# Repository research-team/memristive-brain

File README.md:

# Robot Dream: Memristive brain project ENDSTOP!!!!!

## Problem

The memristive brain project is dedicated to the reimplementation of bio-plausible emotional drives based behavioral strategies in a robotic system, in the other words to solve the embodiment problem for the simulated brain in HPC system. 

During the [NeuCogAr](https://github.com/research-team/NEUCOGAR) project we have managed to develop mammalian emotional drives potential basement for decision making over behavioral strategies. We are doing the validation of overall model of 8 basic emotional states: fear, joy, disgust, humiliation, anger, interest, surprise, distress based on three neuromodulators: noradrenaline, dopamine and serotonin and currently we have managed to validate two states: fear-like and disgust-like. 

The problem is that the bio-plausible simulation of a mammalian brain is really slow and can not be used for real-time processing, but robotic embodiment should be operating real-time. We have started the [Robot Dream](https://github.com/research-team/robot-dream) project to solve this problem still keeping bio-plausibility in integration with real-time robotic system.

A robotic system management system could be implemented using several approaches including reimplementation of mammalian brain structures in electronic schematic. To implement this we have started from the memristive solution of a neuron. Starting from the beginning of 2017 we are developing a memristive implementation of bio-plausible neuronal inhibition and neuromodulation.

The complete documentation on memristive approach could be found [here](https://github.com/research-team/memristive-brain/blob/master/doc/memristive_approach.md).

# Breakthrough 

**AI and robotics**: New architectures of robotic systems, based on the integration of memory and processor in a single chip, capable of memorizing the information and changing accordingly connections between elements within processor will be implemented. This system will be significantly different from the existing computers/robots. The proposed architecture of new generation of robots will be capable of self learning and will not be using traditional software approaches making software development obsolete.

**Brain science/neurophysiology**: In the case of success, neurophysiology will acquire a new tool for modeling of processes in nervous system and brain. An integration of living (neurons) and not living memristive elements will be combined in a hybrid system.This tool will provide an option to better understand processes of the reinforcement and inhibition of signal pathways during supervised and unsupervised learning. Memristors eliminate all physical restrictions of learning algorithms; they allow to “switch off” learning of selected elements, allowing the creation of new neuromorphic machine learning algorithms. 

From the **bionics** perspective, memristor-based artificial synapses could be a part of implantable controllers for artificial organs and prosthesis.
Apart from the breakthrough in the main direction of the research, mentioned above, we expect also to have fundamental results in the following branches:

**Physics/electronics**: The project results will allow to better understand processes, occurring in different memristive devices – new perspective electronic elements. Technological processes of the production of such elements and circuits, as well as processors – memory elements based on them will be developed.  We suppose that the investigation and development of memristive devices could result to the revolution in electronic and computer industries. “Being combined with transistors into hybrid chips, memristors could improve radically properties of digital circuits, without the removal of transistors.
 More effective utilization of transistors could allow to improve properties according to the Moor low, at least during next 10 years, without expensive and becoming continuously more complicated increasing of the integration level in the chip. Finally, memristors could be even a basic stone of new analog circuits, making calculations using the architecture, similar to that of the brain”. [William R.S., How We Found the Missing Memristor. IEEE Spectrum 2008-12-18]. Taking into consideration a grate and continuously increasing interest of scientific centers and commercial laboratories to the implementation of memristors, it is possible to predict that in 5-10 years memristors will be one of the most common elements of electronic circuits.

**Material science/self organization**: it will be investigated new polymer-based materials, allowing to organize structures with distributed electrical properties for the utilization as matrices with adaptive properties.

# Folder structure

+ **demo-stand** - contains info about current measuremet schematic. Now not used.
+ **doc** - contains all required documentation
+ **ltspice_libs** - contains all additional components, used in LTSPICE schematics
+ **memristors** - contains information about memristors, used in project
+ **test-circuits** - contains all electrical schematics, connected with this project

[This video](https://youtu.be/JvsyhsOdTj8) contains all info, related to current circuits.

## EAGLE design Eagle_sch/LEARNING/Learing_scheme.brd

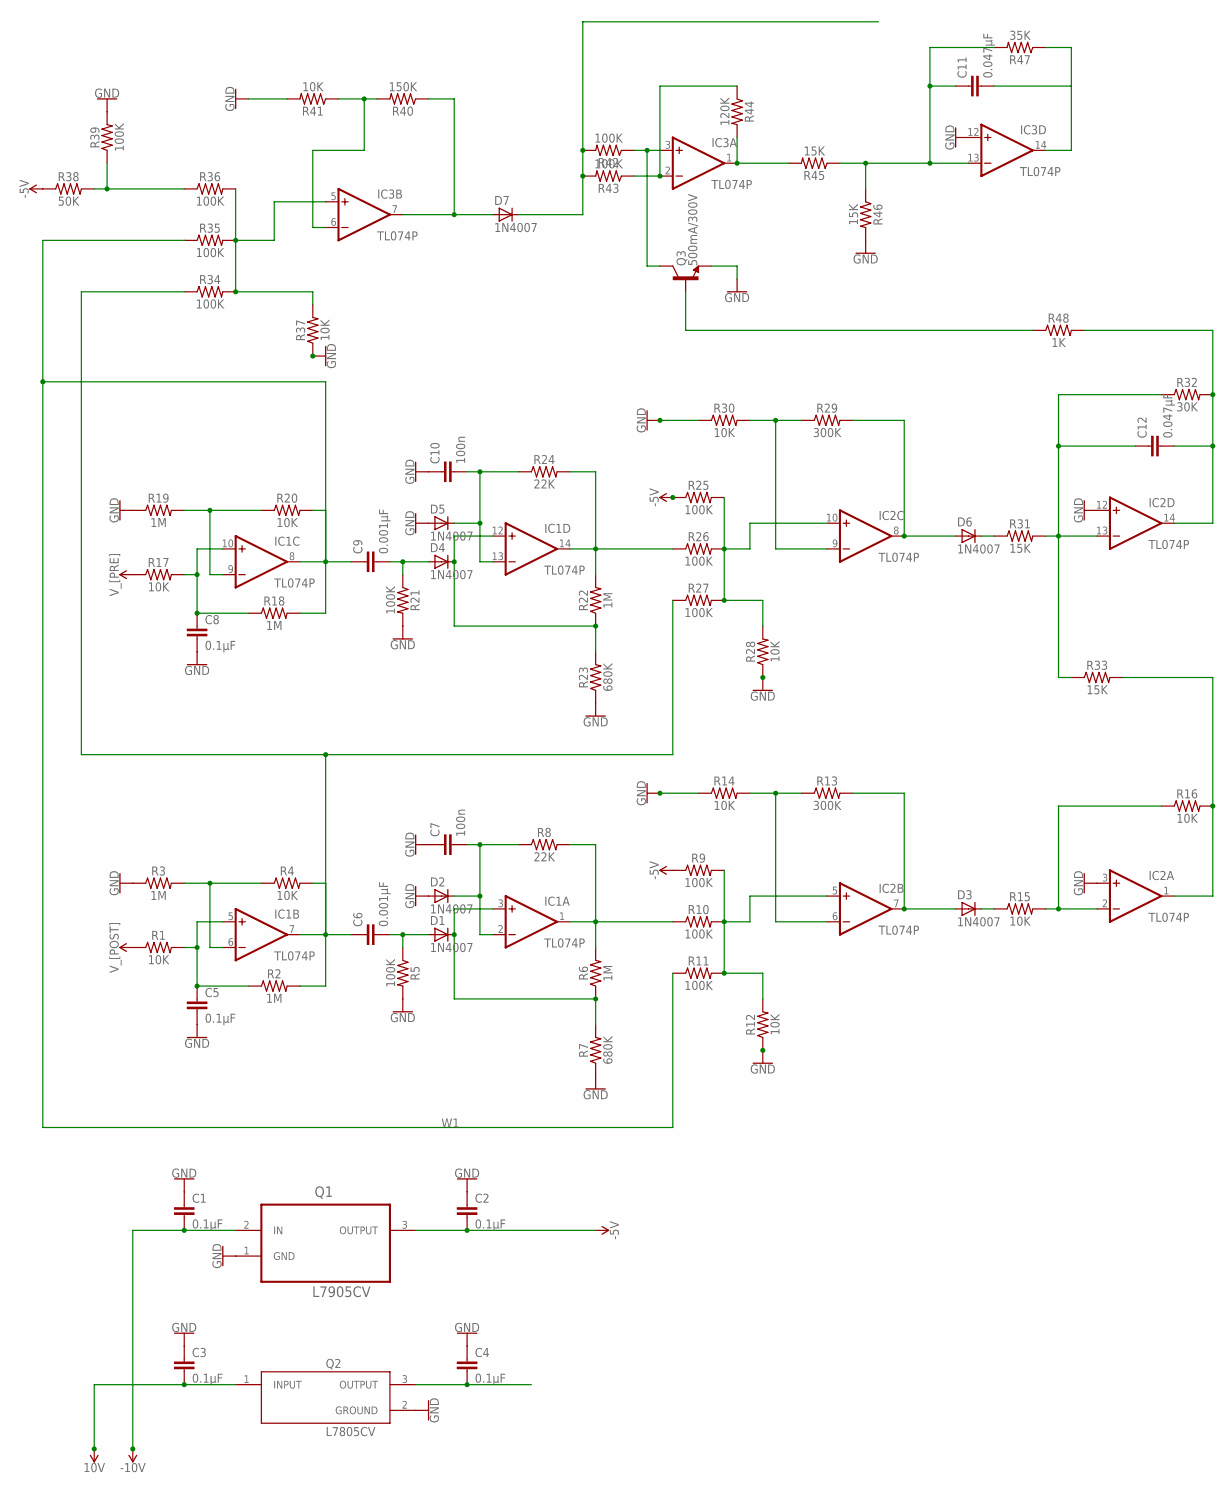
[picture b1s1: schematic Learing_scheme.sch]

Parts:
C1, C2, C3, C4, C5, C8: 0.1µF; 0805
C6, C9: 0.001µF; 0805
C7, C10: 100n; 0805
C11, C12: 0.047µF; 0805
D1, D2, D3, D4, D5, D6, D7: 1N4007; SMA
IC1, IC2, IC3: TL074P; DIL14
Q1: L7905CV; TO254P450X1020X1935-3P
Q2: L7805CV; TO255P1040X460X1968-3
Q3: 500mA/300V; SOT23-3
R1, R4, R12, R14, R15, R16, R17, R20, R28, R30, R37, R41: 10K; 0805
R2, R3, R6, R18, R19, R22: 1M; 0805
R5, R9, R10, R11, R21, R25, R26, R27, R34, R35, R36, R39, R42, R43: 100K; 0805
R7, R23: 680K; 0805
R8, R24: 22K; 0805
R13, R29: 300K; 0805
R31, R33, R45, R46: 15K; 0805
R32: 30K; 0805
R38: 50K; 0805
R40: 150K; 0805
R44: 120K; 0805
R47: 35K; 0805
R48: 1K; 0805

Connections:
12V: C1.2, C2.2, C3.2, Q1.2 (IN), Q1.3 (OUTPUT), Q2.1 (INPUT), R1.1, R9.1, R17.1, R25.1, R38.1
GND: C1.1, C2.1, C3.1, C4.1, C5.2, C7.1, C8.2, C10.1, D2.A, D5.A, IC2.3 (+IN), IC2.12 (+IN), IC3.12 (+IN), Q1.1 (GND), Q2.2 (GROUND), Q3.2 (E), R3.1, R5.2, R7.1, R12.1, R19.1, R21.2, R23.1, R28.1, R37.1, R39.2, R41.2, R46.2
unnamed: C5.1, IC1.5 (+IN), R1.2, R2.1
unnamed: C6.1, IC1.7 (OUT), R2.2, R4.2, R27.1, R34.1
unnamed: IC1.6 (-IN), R3.2, R4.1
unnamed: C4.2, Q2.3 (OUTPUT)
unnamed: D7.A, IC3.7 (OUT), R40.1
unnamed: C6.2, D1.A, R5.1
unnamed: C7.2, D2.K (C), IC1.2 (-IN), R8.1
unnamed: IC1.1 (OUT), R6.2, R8.2, R10.1
unnamed: D1.K (C), IC1.3 (+IN), R6.1, R7.2
unnamed: IC2.5 (+IN), R9.2, R10.2, R11.2, R12.2
unnamed: D3.A, IC2.7 (OUT), R13.2
unnamed: IC2.6 (-IN), R13.1, R14.2
unnamed: D3.K (C), R15.1
unnamed: IC2.2 (-IN), R15.2, R16.1
unnamed: IC2.1 (OUT), R16.2, R33.2
unnamed: C8.1, IC1.10 (+IN), R17.2, R18.1
unnamed: IC3.5 (+IN), R34.2, R35.2, R36.2, R37.2
unnamed: IC1.9 (-IN), R19.2, R20.1
unnamed: C9.2, D4.A, R21.1
unnamed: IC1.14 (OUT), R22.2, R24.2, R26.1
unnamed: D4.K (C), IC1.12 (+IN), R22.1, R23.2
unnamed: C10.2, D5.K (C), IC1.13 (-IN), R24.1
unnamed: IC2.10 (+IN), R25.2, R26.2, R27.2, R28.2
unnamed: D6.A, IC2.8 (OUT), R29.2
unnamed: IC2.9 (-IN), R29.1, R30.2
unnamed: D6.K (C), R31.1
unnamed: C12.1, IC2.13 (-IN), R31.2, R32.1, R33.1
unnamed: C12.2, IC2.14 (OUT), R32.2, R48.2
unnamed: R36.1, R38.2, R39.1
unnamed: IC3.6 (-IN), R40.2, R41.1
unnamed: IC3.3 (+IN), Q3.3 (C), R42.1
unnamed: D7.K (C), R42.2, R43.2
unnamed: IC3.2 (-IN), R43.1, R44.1
unnamed: IC3.1 (OUT), R44.2, R45.2
unnamed: C11.2, IC3.14 (OUT), R47.1
unnamed: C11.1, IC3.13 (-IN), R45.1, R46.1, R47.2
unnamed: Q3.1 (B), R48.1
V+: IC1.4 (V+), IC2.4 (V+), IC3.4 (V+)
V-: IC1.11 (V-), IC2.11 (V-), IC3.11 (V-)
W1: C9.1, IC1.8 (OUT), R11.1, R18.2, R20.2, R35.1

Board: 2 copper layers, 73 parts (0 on the bottom side), 42 nets, no tracks yet.

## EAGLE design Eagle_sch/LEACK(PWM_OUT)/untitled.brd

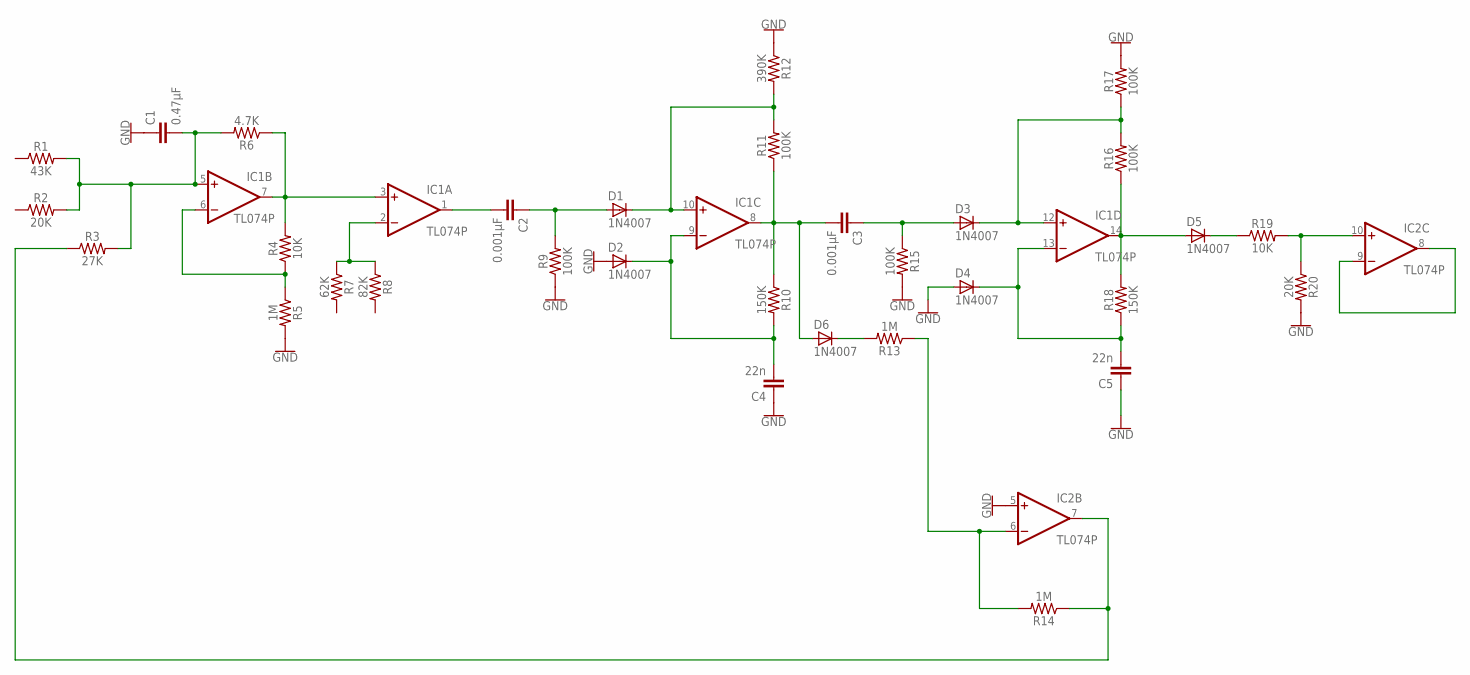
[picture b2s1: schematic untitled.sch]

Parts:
C1: 0.47µF; 0805
C2, C3: 0.001µF; 0805
C4, C5: 22n; 0805
D1, D2, D3, D4, D5, D6: 1N4007; SMA
IC1, IC2: TL074P; DIL14
R1: 43K; 0805
R2, R20: 20K; 0805
R3: 27K; 0805
R4, R19: 10K; 0805
R5, R13, R14: 1M; 0805
R6: 4.7K; 0805
R7: 62K; 0805
R8: 82K; 0805
R9, R11, R15, R16, R17: 100K; 0805
R10, R18: 150K; 0805
R12: 390K; 0805

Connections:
GND: C1.1, C4.1, C5.1, D2.A, D4.A, IC2.5 (+IN), R5.2, R9.1, R12.1, R15.2, R17.2, R20.2
unnamed: C1.2, IC1.5 (+IN), R1.2, R2.2, R3.2, R6.2
unnamed: IC1.3 (+IN), IC1.7 (OUT), R4.2, R6.1
unnamed: IC1.6 (-IN), R4.1, R5.1
unnamed: IC1.2 (-IN), R7.1, R8.1
unnamed: C2.2, IC1.1 (OUT)
unnamed: C2.1, D1.A, R9.2
unnamed: D1.K (C), IC1.10 (+IN), R11.2, R12.2
unnamed: C3.2, D6.A, IC1.8 (OUT), R10.1, R11.1
unnamed: C4.2, D2.K (C), IC1.9 (-IN), R10.2
unnamed: C3.1, D3.A, R15.1
unnamed: C5.2, D4.K (C), IC1.13 (-IN), R18.1
unnamed: D5.A, IC1.14 (OUT), R16.1, R18.2
unnamed: D3.K (C), IC1.12 (+IN), R16.2, R17.1
unnamed: D5.K (C), R19.1
unnamed: IC2.10 (+IN), R19.2, R20.1
unnamed: IC2.8 (OUT), IC2.9 (-IN)
unnamed: D6.K (C), R13.2
unnamed: IC2.6 (-IN), R13.1, R14.2
unnamed: IC2.7 (OUT), R3.1, R14.1
V+: IC1.4 (V+), IC2.4 (V+)
V-: IC1.11 (V-), IC2.11 (V-)

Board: 2 copper layers, 33 parts (0 on the bottom side), 22 nets, no tracks yet.

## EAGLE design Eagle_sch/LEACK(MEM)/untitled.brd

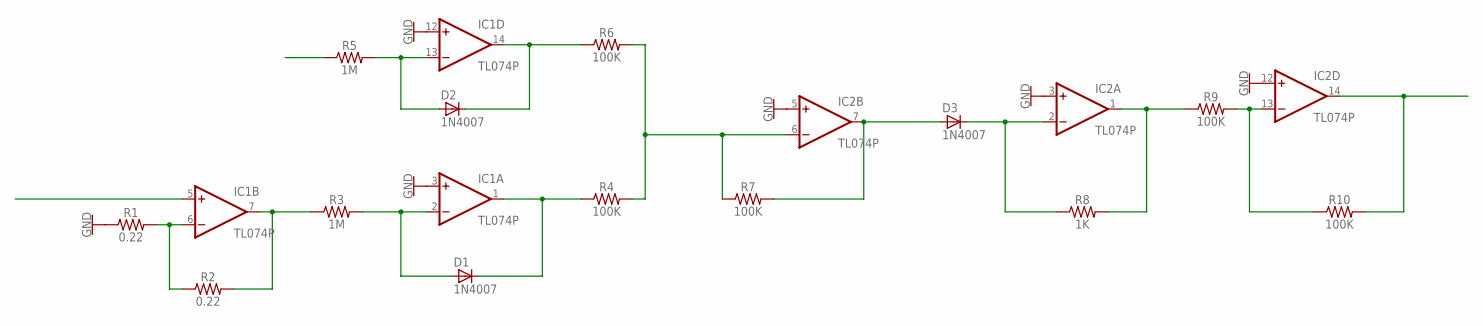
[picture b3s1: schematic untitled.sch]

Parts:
D1, D2, D3: 1N4007; SMA
IC1, IC2: TL074P; DIL14
R1, R2: 0.22; 0805
R3, R5: 1M; 0805
R4, R6, R7, R9, R10: 100K; 0805
R8: 1K; 0805

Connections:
GND: IC1.3 (+IN), IC1.12 (+IN), IC2.3 (+IN), IC2.5 (+IN), IC2.12 (+IN), R1.1
unnamed: IC1.6 (-IN), R1.2, R2.1
unnamed: IC1.7 (OUT), R2.2, R3.1
unnamed: D1.A, IC1.2 (-IN), R3.2
unnamed: D1.K (C), IC1.1 (OUT), R4.1
unnamed: D2.K (C), IC1.14 (OUT), R6.1
unnamed: D2.A, IC1.13 (-IN), R5.2
unnamed: D3.A, IC2.7 (OUT), R7.2
unnamed: D3.K (C), IC2.2 (-IN), R8.1
unnamed: IC2.6 (-IN), R4.2, R6.2, R7.1
unnamed: IC2.1 (OUT), R8.2, R9.1
unnamed: IC2.13 (-IN), R9.2, R10.1
unnamed: IC2.14 (OUT), R10.2
V+: IC1.4 (V+), IC2.4 (V+)
V-: IC1.11 (V-), IC2.11 (V-)

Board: 2 copper layers, 15 parts (0 on the bottom side), 15 nets, no tracks yet.

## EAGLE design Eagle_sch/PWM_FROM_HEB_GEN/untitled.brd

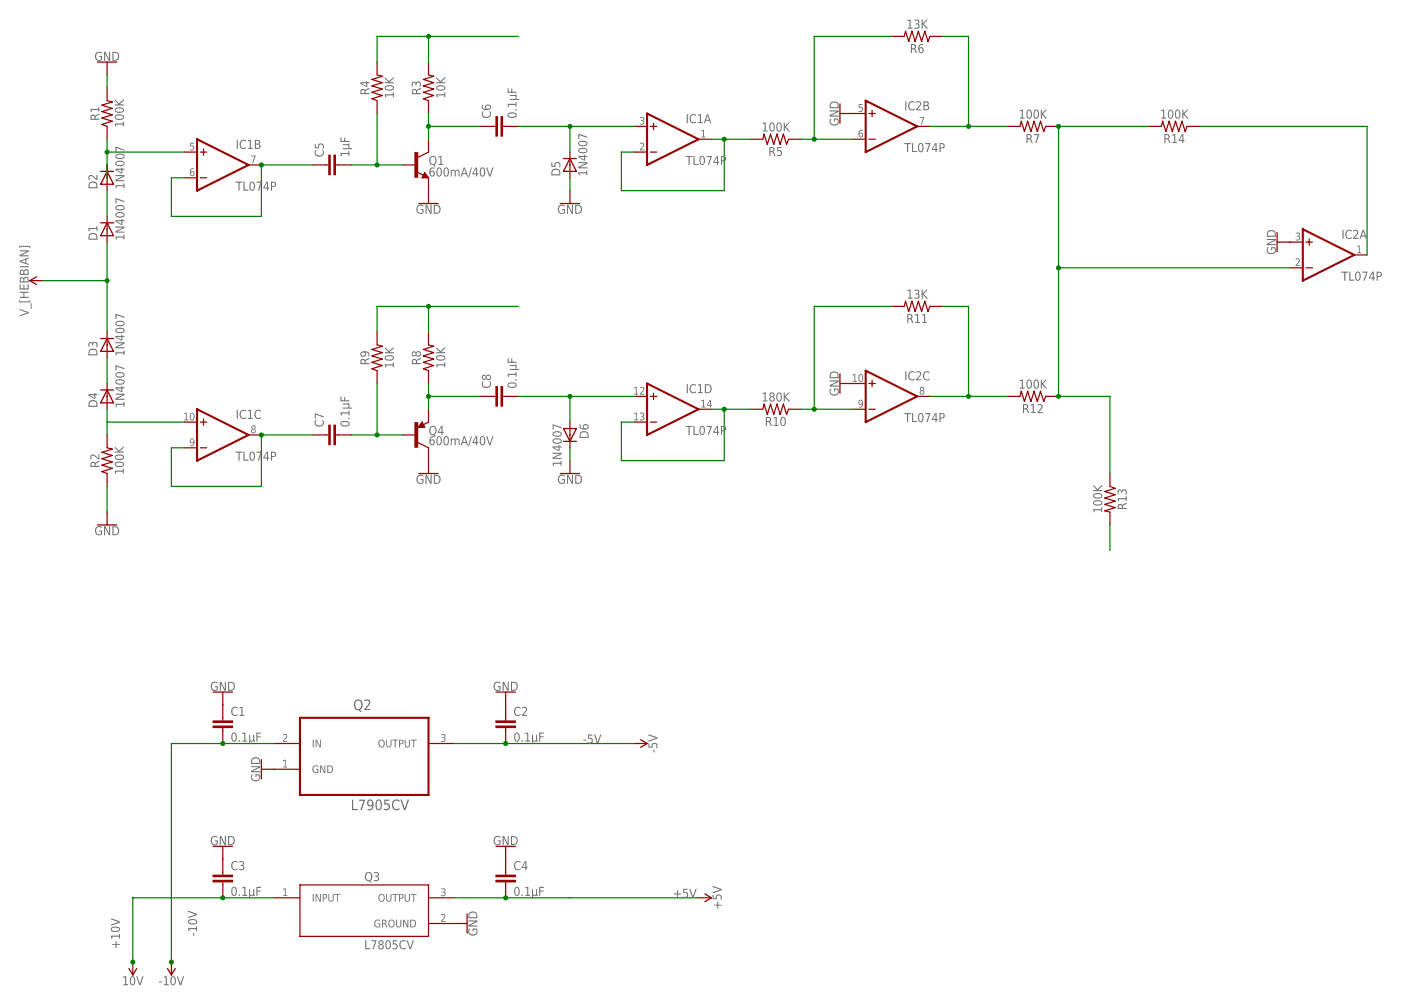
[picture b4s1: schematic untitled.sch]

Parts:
C1, C2, C3, C4, C6, C7, C8: 0.1µF; 0805
C5: 1µF; 0805
D1, D2, D3, D4, D5, D6: 1N4007; SMA
IC1, IC2: TL074P; DIL14
Q1, Q4: 600mA/40V; SOT23-3
Q2: L7905CV; TO254P450X1020X1935-3P
Q3: L7805CV; TO255P1040X460X1968-3
R1, R2, R5, R7, R12, R13, R14: 100K; 0805
R3, R4, R8, R9: 10K; 0805
R6, R11: 13K; 0805
R10: 180K; 0805

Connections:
12V: D1.A, D3.K (C)
+10V: C3.2, Q3.1 (INPUT)
-5V: C2.2, Q2.3 (OUTPUT)
-10V: C1.2, Q2.2 (IN)
GND: C1.1, C2.1, C3.1, C4.1, D5.A, D6.K (C), IC2.3 (+IN), IC2.5 (+IN), IC2.10 (+IN), Q1.2 (E), Q2.1 (GND), Q3.2 (GROUND), Q4.3 (C), R1.2, R2.1
unnamed: D1.K (C), D2.A
unnamed: D2.K (C), IC1.5 (+IN), R1.1
unnamed: C5.1, IC1.6 (-IN), IC1.7 (OUT)
unnamed: D3.A, D4.K (C)
unnamed: D4.A, R2.2
unnamed: C5.2, Q1.1 (B), R4.1
unnamed: C6.1, Q1.3 (C), R3.1
unnamed: R3.2, R4.2
unnamed: C4.2, Q3.3 (OUTPUT)
unnamed: C6.2, D5.K (C), IC1.3 (+IN)
unnamed: IC1.1 (OUT), IC1.2 (-IN), R5.2
unnamed: IC2.6 (-IN), R5.1, R6.2
unnamed: IC2.7 (OUT), R6.1, R7.2
unnamed: C7.1, IC1.8 (OUT), IC1.9 (-IN)
unnamed: C7.2, Q4.1 (B), R9.1
unnamed: C8.1, Q4.2 (E), R8.1
unnamed: R8.2, R9.2
unnamed: C8.2, D6.A, IC1.12 (+IN)
unnamed: IC1.13 (-IN), IC1.14 (OUT), R10.2
unnamed: IC2.9 (-IN), R10.1, R11.2
unnamed: IC2.8 (OUT), R11.1, R12.2
unnamed: IC2.2 (-IN), R7.1, R12.1, R13.1, R14.2
unnamed: IC2.1 (OUT), R14.1
V+: IC1.4 (V+), IC2.4 (V+)
V-: IC1.11 (V-), IC2.11 (V-)

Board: 2 copper layers, 34 parts (0 on the bottom side), 30 nets, no tracks yet.

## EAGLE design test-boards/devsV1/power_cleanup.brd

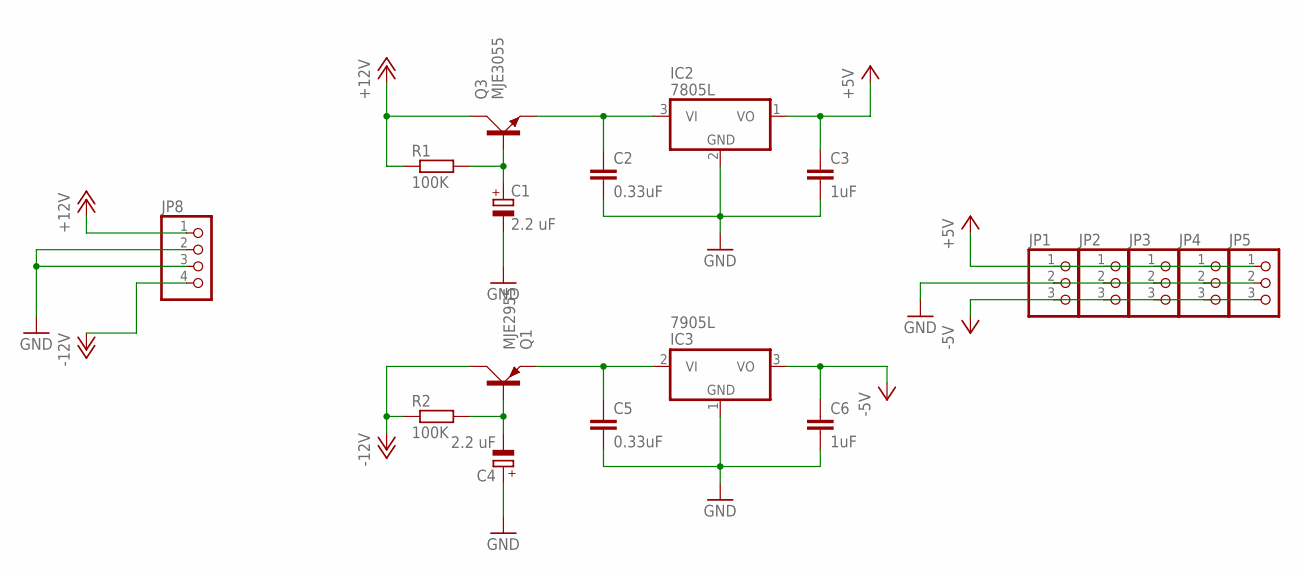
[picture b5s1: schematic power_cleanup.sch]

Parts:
C1, C4: 2.2 uF; E2-5
C2, C5: 0.33uF; C025-025X050
C3, C6: 1uF; C025-025X050
IC2: 7805L; TO92
IC3: 7905L; TO92
JP1, JP2, JP3, JP4, JP5: PINHD-1X3; 1X03
JP8: PINHD-1X4; 1X04
Q1: MJE2955; TO220AV
Q3: MJE3055; TO220AV
R1, R2: 100K; 0207/10

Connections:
+5V: C3.1, IC2.1 (VO), JP1.1, JP2.1, JP3.1, JP4.1, JP5.1
+12V: JP8.1, Q3.C, R1.1
-5V: C6.1, IC3.3 (VO), JP1.3, JP2.3, JP3.3, JP4.3, JP5.3
-12V: JP8.4, Q1.C, R2.1
GND: C1.-, C2.2, C3.2, C4.+, C5.2, C6.2, IC2.2 (GND), IC3.1 (GND), JP1.2, JP2.2, JP3.2, JP4.2, JP5.2, JP8.2, JP8.3
unnamed: C1.+, Q3.B, R1.2
unnamed: C2.1, IC2.3 (VI), Q3.E
unnamed: C4.-, Q1.B, R2.2
unnamed: C5.1, IC3.2 (VI), Q1.E

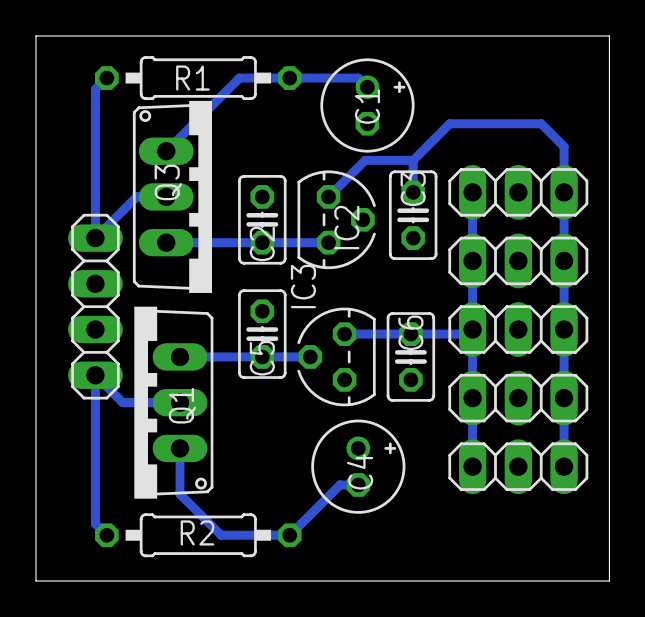
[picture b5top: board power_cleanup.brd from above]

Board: 2 copper layers, 31.9 x 30.3 mm, 18 parts (0 on the bottom side), 9 nets.

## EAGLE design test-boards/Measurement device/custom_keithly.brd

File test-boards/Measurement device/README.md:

# Download 
1)[AD eaglecad devices lib1](http://www.element14.com/community/servlet/JiveServlet/download/38-101421)  
2)[AD eaglecad devices lib2](http://www.element14.com/community/servlet/JiveServlet/download/38-104498) and 
3)[TI eaglecad devices lib](http://www.element14.com/community/servlet/JiveServlet/download/38-101426) 
4)[micro-stm_v3](http://eagle.autodesk.com/eagle/download/109)
before working on schematic

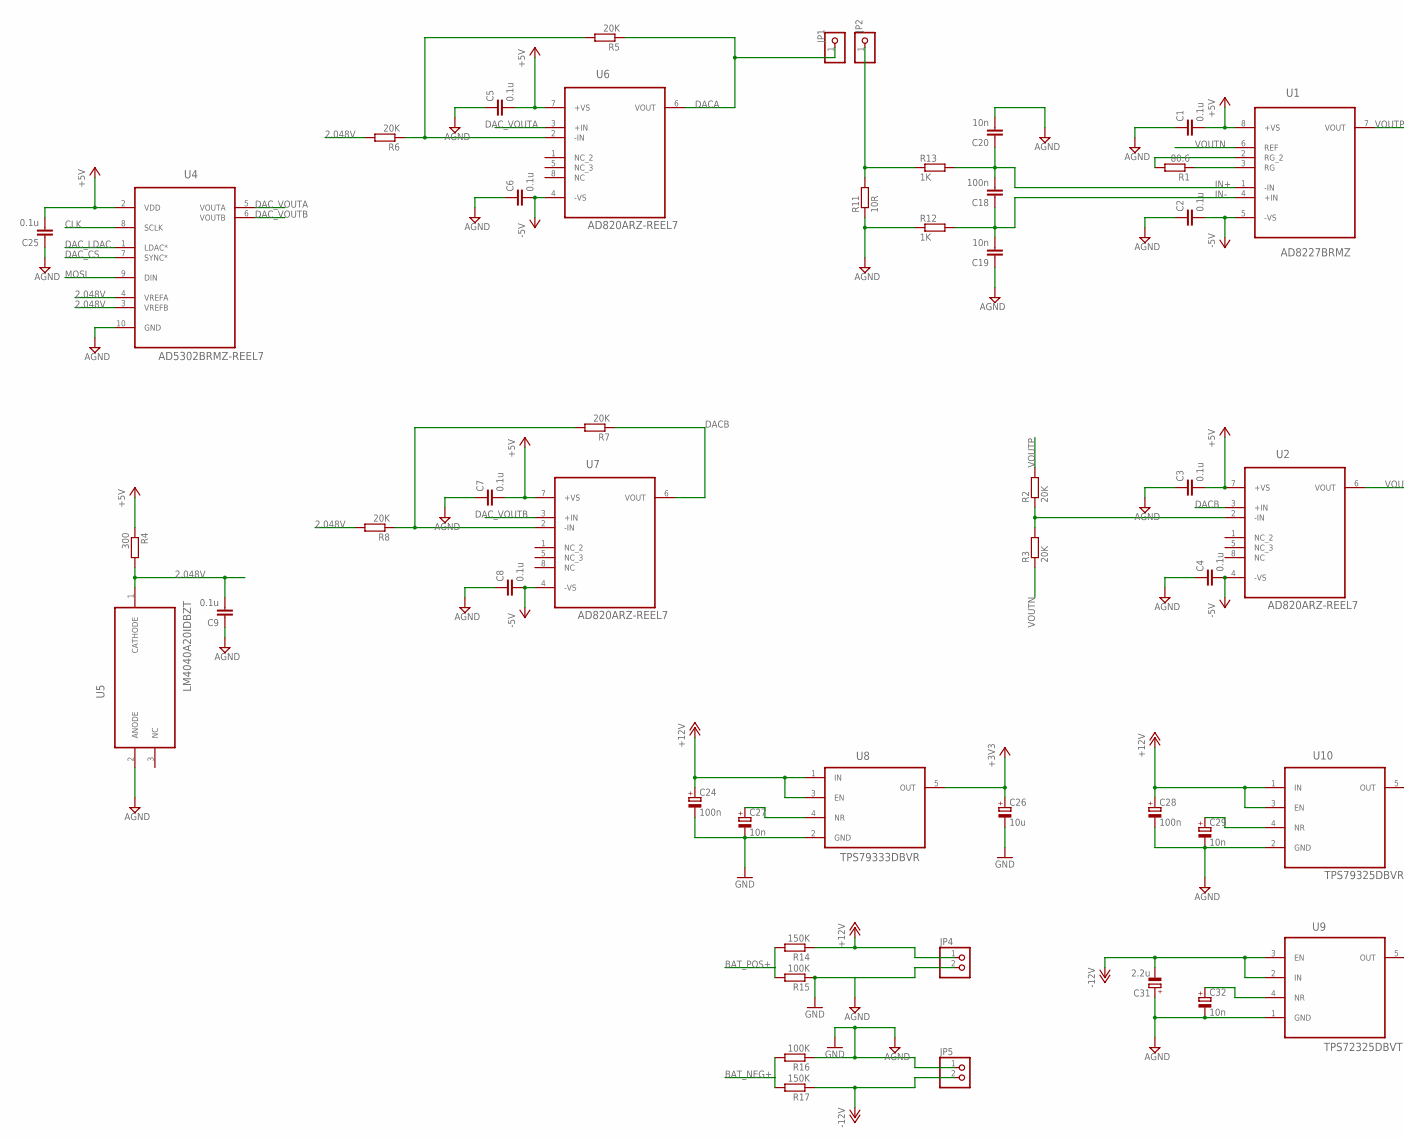
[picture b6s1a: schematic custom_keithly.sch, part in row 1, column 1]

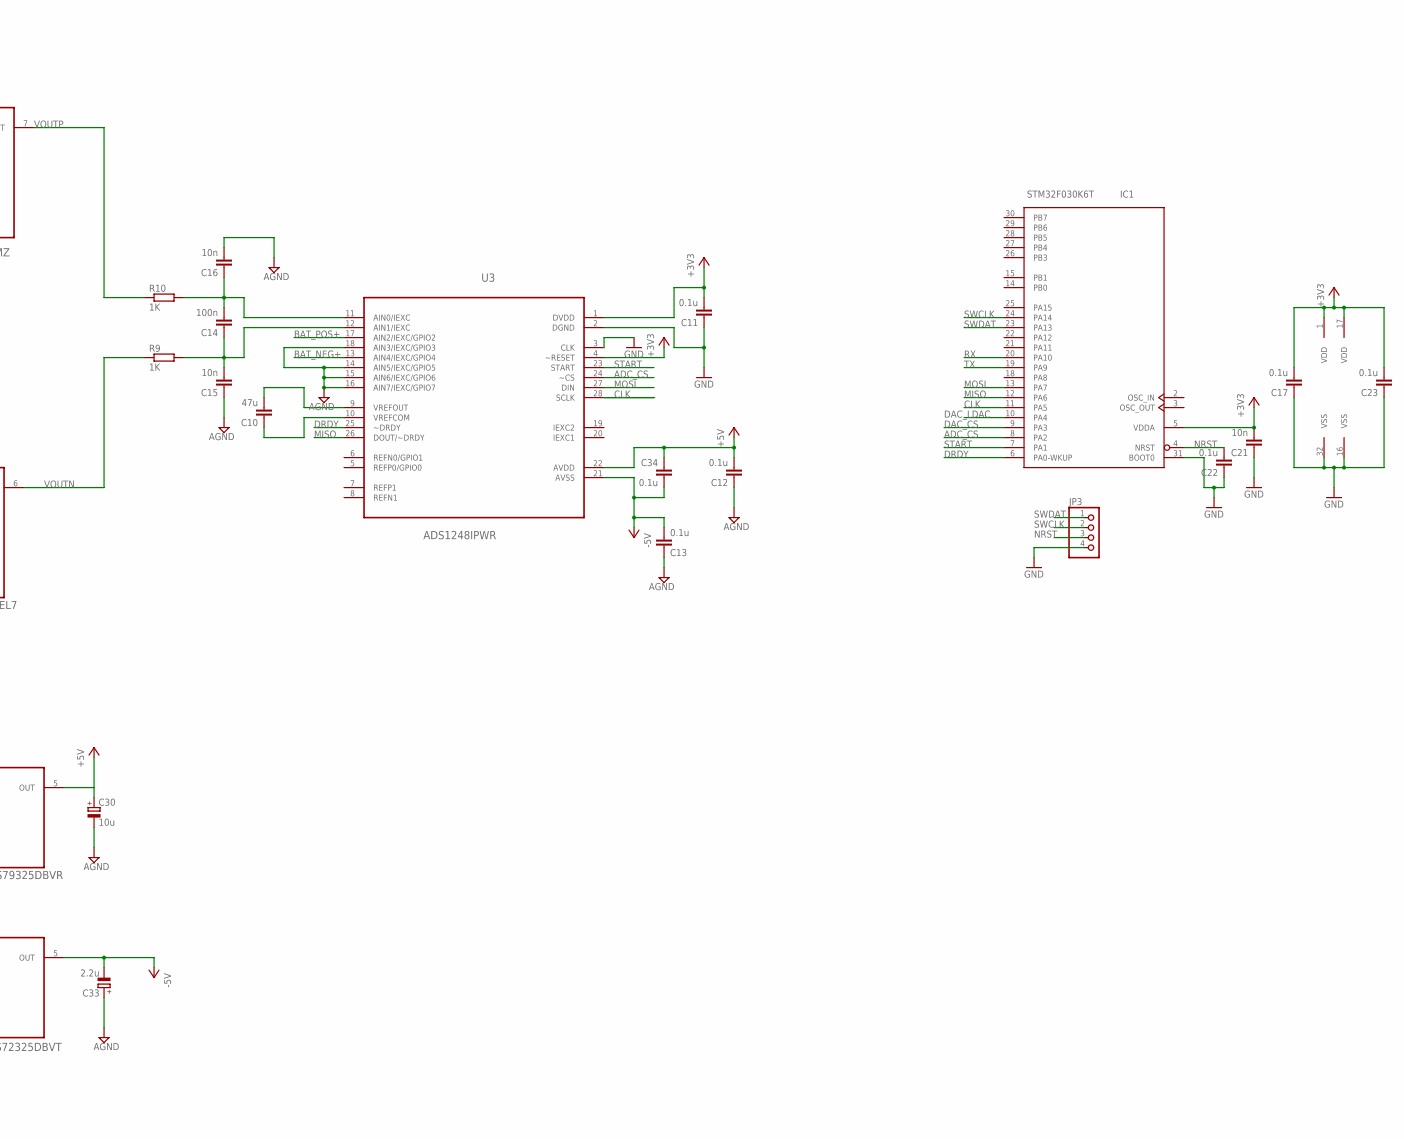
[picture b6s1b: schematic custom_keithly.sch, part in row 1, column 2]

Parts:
C1, C2, C3, C4, C5, C6, C7, C8, C9, C11, C12, C13, C17, C22, C23, C25, C34: 0.1u; C0603K
C10: 47u; C0603K
C14, C18: 100n; C0603K
C15, C16, C19, C20, C21: 10n; C0603K
C24, C28: 100n; CT3216
C26, C30: 10u; CT3216
C27, C29, C32: 10n; CT3216
C31, C33: 2.2u; CT3216
IC1: STM32F030K6T; LQFP32
JP1, JP2: PINHD-1X1; 1X01
JP3: PINHD-1X4; 1X04
JP4, JP5: PINHD-1X2; 1X02
R1: 80.6; R0805
R2, R3, R5, R6, R7, R8: 20K; R0603
R4: 300; R0805
R9, R10, R12, R13: 1K; R0805
R11: 10R; R0805
R14, R17: 150K; R0603
R15, R16: 100K; R0603
U1: AD8227BRMZ; SOP65P490X110-8N
U2, U6, U7: AD820ARZ-REEL7; SOIC127P600X175-8N
U3: ADS1248IPWR; SOP65P640X120-28N
U4: AD5302BRMZ-REEL7; SOP50P490X110-10N
U5: LM4040A20IDBZT; SOT95P237X112-3N
U8: TPS79333DBVR; SOT95P280X145-5N
U9: TPS72325DBVT; SOT95P280X145-5N
U10: TPS79325DBVR; SOT95P280X145-5N

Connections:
2.048V: C9.2, R4.2, R6.2, R8.2, U4.3 (VREFB), U4.4 (VREFA), U5.1 (CATHODE)
+3V3: C11.2, C17.2, C21.2, C23.2, C26.+, IC1.1 (VDD), IC1.5 (VDDA), IC1.17 (VDD), U3.1 (DVDD), U3.4 (~RESET), U8.5 (OUT)
+5V: C1.2, C3.2, C5.2, C7.2, C12.2, C25.2, C30.+, C34.1, R4.1, U1.8 (+VS), U2.7 (+VS), U3.22 (AVDD), U4.2 (VDD), U6.7 (+VS), U7.7 (+VS), U10.5 (OUT)
+12V: C24.+, C28.+, JP4.1, R14.1, U8.1 (IN), U8.3 (EN), U10.1 (IN), U10.3 (EN)
-5V: C2.2, C4.2, C6.2, C8.2, C13.2, C33.-, C34.2, U1.5 (-VS), U2.4 (-VS), U3.21 (AVSS), U6.4 (-VS), U7.4 (-VS), U9.5 (OUT)
-12V: C31.-, JP5.2, R17.1, U9.2 (IN), U9.3 (EN)
ADC_CS: IC1.8 (PA2), U3.24 (~CS)
AGND: C1.1, C2.1, C3.1, C4.1, C5.1, C6.1, C7.1, C8.1, C9.1, C12.1, C13.1, C15.1, C16.2, C19.1, C20.2, C25.1, C28.-, C29.-, C30.-, C31.+, C32.-, C33.+, JP4.2, R11.1, R12.1, R15.1, U3.14 (AIN5/IEXC/GPIO5), U3.15 (AIN6/IEXC/GPIO6), U3.16 (AIN7/IEXC/GPIO7), U3.18 (AIN3/IEXC/GPIO3), U4.10 (GND), U5.2 (ANODE), U9.1 (GND), U10.2 (GND)
BAT_NEG+: R16.2, R17.2, U3.13 (AIN4/IEXC/GPIO4)
BAT_POS+: R14.2, R15.2, U3.17 (AIN2/IEXC/GPIO2)
CLK: IC1.11 (PA5), U3.28 (SCLK), U4.8 (SCLK)
DACA: JP1.1, R5.1, U6.6 (VOUT)
DACB: R7.1, U2.3 (+IN), U7.6 (VOUT)
DAC_CS: IC1.9 (PA3), U4.7 (SYNC*)
DAC_LDAC: IC1.10 (PA4), U4.1 (LDAC*)
DAC_VOUTA: U4.5 (VOUTA), U6.3 (+IN)
DAC_VOUTB: U4.6 (VOUTB), U7.3 (+IN)
DRDY: IC1.6 (PA0-WKUP), U3.25 (~DRDY)
GND: C11.1, C17.1, C21.1, C22.1, C23.1, C24.-, C26.-, C27.-, IC1.16 (VSS), IC1.31 (BOOT0), IC1.32 (VSS), JP3.4, JP5.1, R16.1, U3.2 (DGND), U3.3 (CLK), U8.2 (GND)
IN+: C18.2, C20.1, R13.2, U1.1 (-IN)
IN-: C18.1, C19.2, R12.2, U1.4 (+IN)
MISO: IC1.12 (PA6), U3.26 (DOUT/~DRDY)
MOSI: IC1.13 (PA7), U3.27 (DIN), U4.9 (DIN)
unnamed: R1.2, U1.2 (RG_2)
unnamed: R1.1, U1.3 (RG)
unnamed: R2.1, R3.2, U2.2 (-IN)
unnamed: C10.2, U3.9 (VREFOUT)
unnamed: R5.2, R6.1, U6.2 (-IN)
unnamed: C10.1, U3.10 (VREFCOM)
unnamed: R7.2, R8.1, U7.2 (-IN)
unnamed: C14.1, C15.2, R9.2, U3.12 (AIN1/IEXC)
unnamed: C14.2, C16.1, R10.2, U3.11 (AIN0/IEXC)
unnamed: JP2.1, R11.2, R13.1
unnamed: C29.+, U10.4 (NR)
unnamed: C32.+, U9.4 (NR)
NRST: C22.2, IC1.4 (NRST), JP3.3
RX: IC1.20 (PA10)
START: IC1.7 (PA1), U3.23 (START)
SWCLK: IC1.24 (PA14), JP3.2
SWDAT: IC1.23 (PA13), JP3.1
TX: IC1.19 (PA9)
VOUTN: R3.1, R9.1, U1.6 (REF), U2.6 (VOUT)
VOUTP: R2.2, R10.1, U1.7 (VOUT)

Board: 4 copper layers, 67 parts (0 on the bottom side), 41 nets, no tracks yet.

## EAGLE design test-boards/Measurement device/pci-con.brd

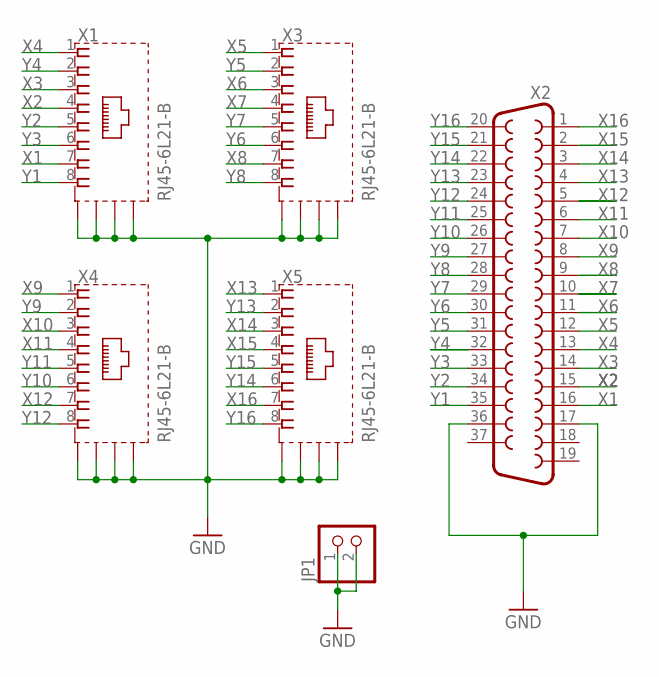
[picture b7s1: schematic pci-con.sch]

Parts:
JP1: PINHD-1X2; 1X02
X1, X3, X4, X5: RJ45-6L21-B; RJ45-SHIELD1
X2: F37HP

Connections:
GND: JP1.1, JP1.2, X1.S1 (S), X1.S2 (S), X1.S3 (S), X1.S4 (S), X2.17, X2.36, X3.S1 (S), X3.S2 (S), X3.S3 (S), X3.S4 (S), X4.S1 (S), X4.S2 (S), X4.S3 (S), X4.S4 (S), X5.S1 (S), X5.S2 (S), X5.S3 (S), X5.S4 (S)
X1: X1.7, X2.16
X2: X1.4, X2.15
X3: X1.3, X2.14
X4: X1.1, X2.13
X5: X2.12, X3.1
X6: X2.11, X3.3
X7: X2.10, X3.4
X8: X2.9, X3.7
X9: X2.8, X4.1
X10: X2.7, X4.3
X11: X2.6, X4.4
X12: X2.5, X4.7
X13: X2.4, X5.1
X14: X2.3, X5.3
X15: X2.2, X5.4
X16: X2.1, X5.7
Y1: X1.8, X2.35
Y2: X1.5, X2.34
Y3: X1.6, X2.33
Y4: X1.2, X2.32
Y5: X2.31, X3.2
Y6: X2.30, X3.6
Y7: X2.29, X3.5
Y8: X2.28, X3.8
Y9: X2.27, X4.2
Y10: X2.26, X4.6
Y11: X2.25, X4.5
Y12: X2.24, X4.8
Y13: X2.23, X5.2
Y14: X2.22, X5.6
Y15: X2.21, X5.5
Y16: X2.20, X5.8

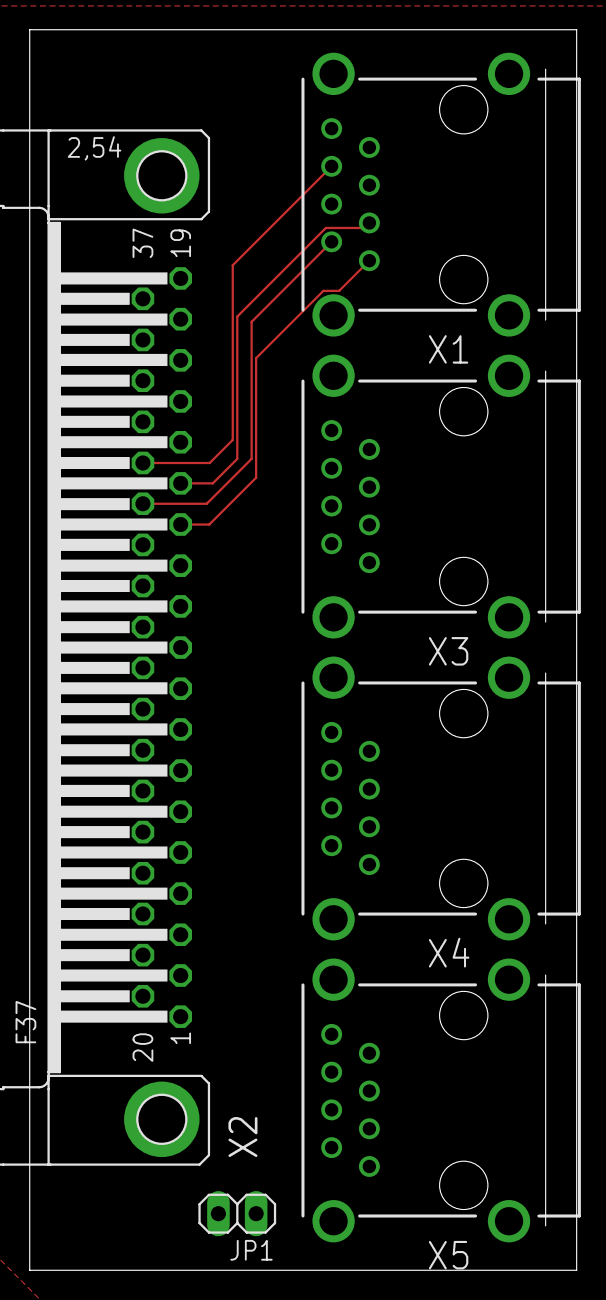
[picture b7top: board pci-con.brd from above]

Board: 2 copper layers, 36.8 x 83.5 mm, 6 parts (0 on the bottom side), 33 nets.

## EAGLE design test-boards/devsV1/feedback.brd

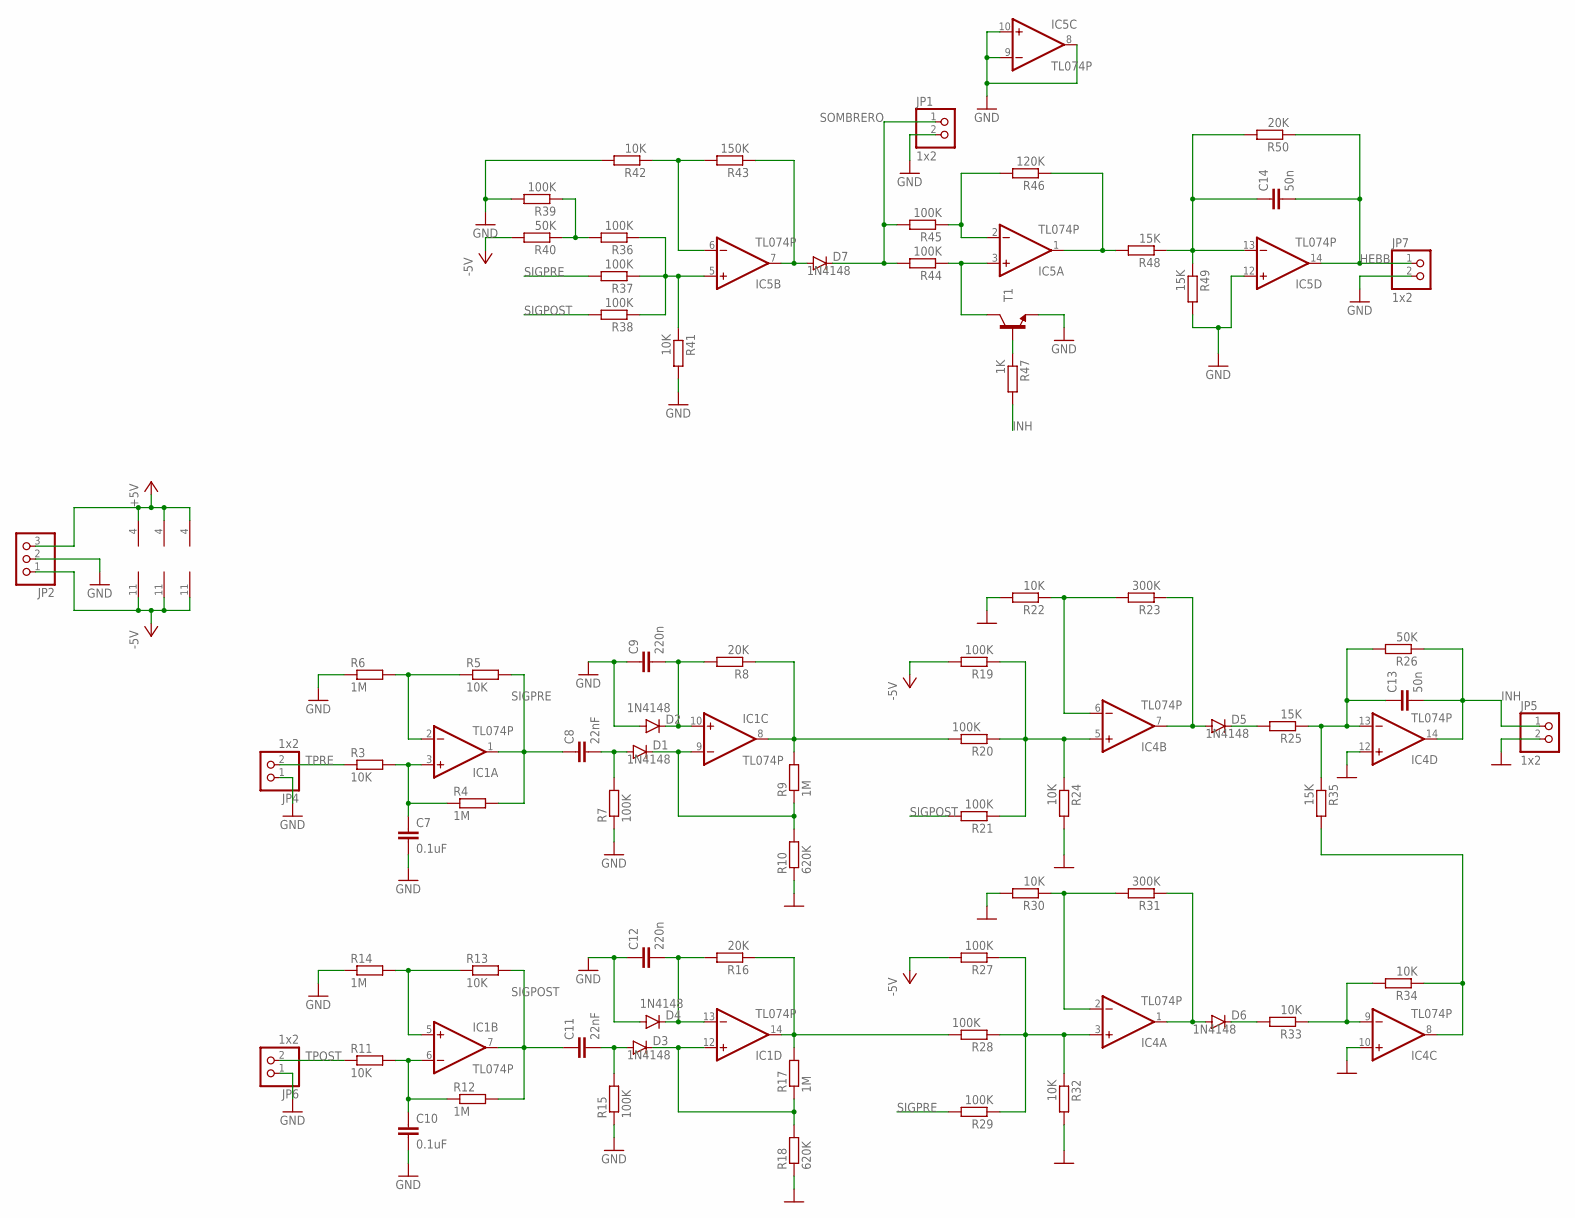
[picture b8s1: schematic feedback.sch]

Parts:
C7, C10: 0.1uF; C050-024X044
C8, C11: 22nF; C050-024X044
C9, C12: 220n; C050-024X044
C13, C14: 50n; C050-024X044
D1, D2, D3, D4, D5, D6, D7: 1N4148; DIODE-1N4148
IC1, IC4, IC5: TL074P; DIL14
JP1, JP4, JP5, JP6, JP7: 1x2; 1X02
JP2: PINHD-1X3; 1X03
R3, R5, R11, R13, R22, R24, R30, R32, R33, R34, R41, R42: 10K; 0207/10
R4, R6, R9, R12, R14, R17: 1M; 0207/10
R7, R15, R19, R20, R21, R27, R28, R29, R36, R37, R38, R39, R44, R45: 100K; 0207/10
R8, R16, R50: 20K; 0207/10
R10, R18: 620K; 0207/10
R23, R31: 300K; 0207/10
R25, R35, R48, R49: 15K; 0207/10
R26, R40: 50K; 0207/10
R43: 150K; 0207/10
R46: 120K; 0207/10
R47: 1K; 0207/10
T1: BC337-25-NPN-TO92-CBE; TO92-CBE

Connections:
+5V: IC1.4 (V+), IC4.4 (V+), IC5.4 (V+), JP2.3
-5V: IC1.11 (V-), IC4.11 (V-), IC5.11 (V-), JP2.1, R19.2, R27.2, R40.2
GND: C7.2, C9.1, C10.2, C12.1, D2.A, D4.A, IC4.10 (+IN), IC4.12 (+IN), IC5.8 (OUT), IC5.9 (-IN), IC5.10 (+IN), IC5.12 (+IN), JP1.2, JP2.2, JP4.1, JP5.2, JP6.1, JP7.2, R6.1, R7.1, R10.1, R14.1, R15.1, R18.1, R22.2, R24.2, R30.2, R32.2, R39.2, R41.2, R42.2, R49.2, T1.E
HEBB: C14.2, IC5.14 (OUT), JP7.1, R50.1
INH: C13.2, IC4.14 (OUT), JP5.1, R26.1, R47.2
unnamed: C7.1, IC1.3 (+IN), R3.2, R4.1
unnamed: IC5.5 (+IN), R36.1, R37.1, R38.1, R41.1
unnamed: IC4.5 (+IN), R19.1, R20.1, R21.1, R24.1
unnamed: IC1.2 (-IN), R5.1, R6.2
unnamed: C8.2, D1.A, R7.2
unnamed: C10.1, IC1.6 (-IN), R11.2, R12.1
unnamed: C9.2, D2.C, IC1.10 (+IN), R8.2
unnamed: D1.C, IC1.9 (-IN), R9.1, R10.2
unnamed: IC1.8 (OUT), R8.1, R9.2, R20.2
unnamed: R36.2, R39.1, R40.1
unnamed: IC4.6 (-IN), R22.1, R23.2
unnamed: IC1.5 (+IN), R13.1, R14.2
unnamed: C11.2, D3.A, R15.2
unnamed: C12.2, D4.C, IC1.13 (-IN), R16.2
unnamed: IC1.14 (OUT), R16.1, R17.2, R28.2
unnamed: D3.C, IC1.12 (+IN), R17.1, R18.2
unnamed: D5.A, IC4.7 (OUT), R23.1
unnamed: D5.C, R25.2
unnamed: C14.1, IC5.13 (-IN), R48.1, R49.1, R50.2
unnamed: C13.1, IC4.13 (-IN), R25.1, R26.2, R35.1
unnamed: IC4.3 (+IN), R27.1, R28.1, R29.1, R32.1
unnamed: IC5.6 (-IN), R42.1, R43.2
unnamed: D6.A, IC4.1 (OUT), R31.1
unnamed: D6.C, R33.2
unnamed: IC4.9 (-IN), R33.1, R34.2
unnamed: IC4.8 (OUT), R34.1, R35.2
unnamed: IC4.2 (-IN), R30.1, R31.2
unnamed: D7.A, IC5.7 (OUT), R43.1
unnamed: IC5.3 (+IN), R44.1, T1.C
unnamed: IC5.2 (-IN), R45.1, R46.2
unnamed: IC5.1 (OUT), R46.1, R48.2
unnamed: R47.1, T1.B
SIGPOST: C11.1, IC1.7 (OUT), R12.2, R13.2, R21.2, R38.2
SIGPRE: C8.1, IC1.1 (OUT), R4.2, R5.2, R29.2, R37.2
SOMBRERO: D7.C, JP1.1, R44.2, R45.2
TPOST: JP6.2, R11.1
TPRE: JP4.2, R3.1

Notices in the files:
parts and their libraries:
SparkFun-Resistors: Licensing: Creative Commons ShareAlike 4.0 International - https://creativecommons.org/licenses/by-sa/4.0
